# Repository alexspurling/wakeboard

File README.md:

# Wakeboard

A custom Kicad PCB based on the ESP32 and LIS3DH accelerometer. I built this to use as a low power device to detect when my washing machine starts and to send me a notification when it ends.

All files are open source under the Apache Licence 2.0

## Instructions for adding components

Since I wanted to order the PCB with JLCPCB, I wanted to ensure I picked parts that they have in stock. To do this, I used [easyeda2kicad](https://github.com/uPesy/easyeda2kicad.py) to pull the schematic, footprint and 3D model of a given LCSC part number. To run the script:

```
pip install easyeda2kicad
```

```
easyeda2kicad --full --lcsc_id=C2894897
```

This will copy files from EasyEDA (JLCPCB's own PCB creation tool) and save them into your `Documents/Kicad` directory.

From here, you can add this location as a library into KiCad to make all your downloaded components available:

* In KiCad, Go to Preferences > Configure Paths, and add the environment variables EASYEDA2KICAD :

    Windows : C:/Users/your_username/Documents/Kicad/easyeda2kicad/,
    Linux : /home/your_username/Documents/Kicad/easyeda2kicad/

* Go to Preferences > Manage Symbol Libraries, and Add the global library easyeda2kicad : ${EASYEDA2KICAD}/easyeda2kicad.kicad_sym
* Go to Preferences > Manage Footprint Libraries, and Add the global library easyeda2kicad : ${EASYEDA2KICAD}/easyeda2kicad.pretty

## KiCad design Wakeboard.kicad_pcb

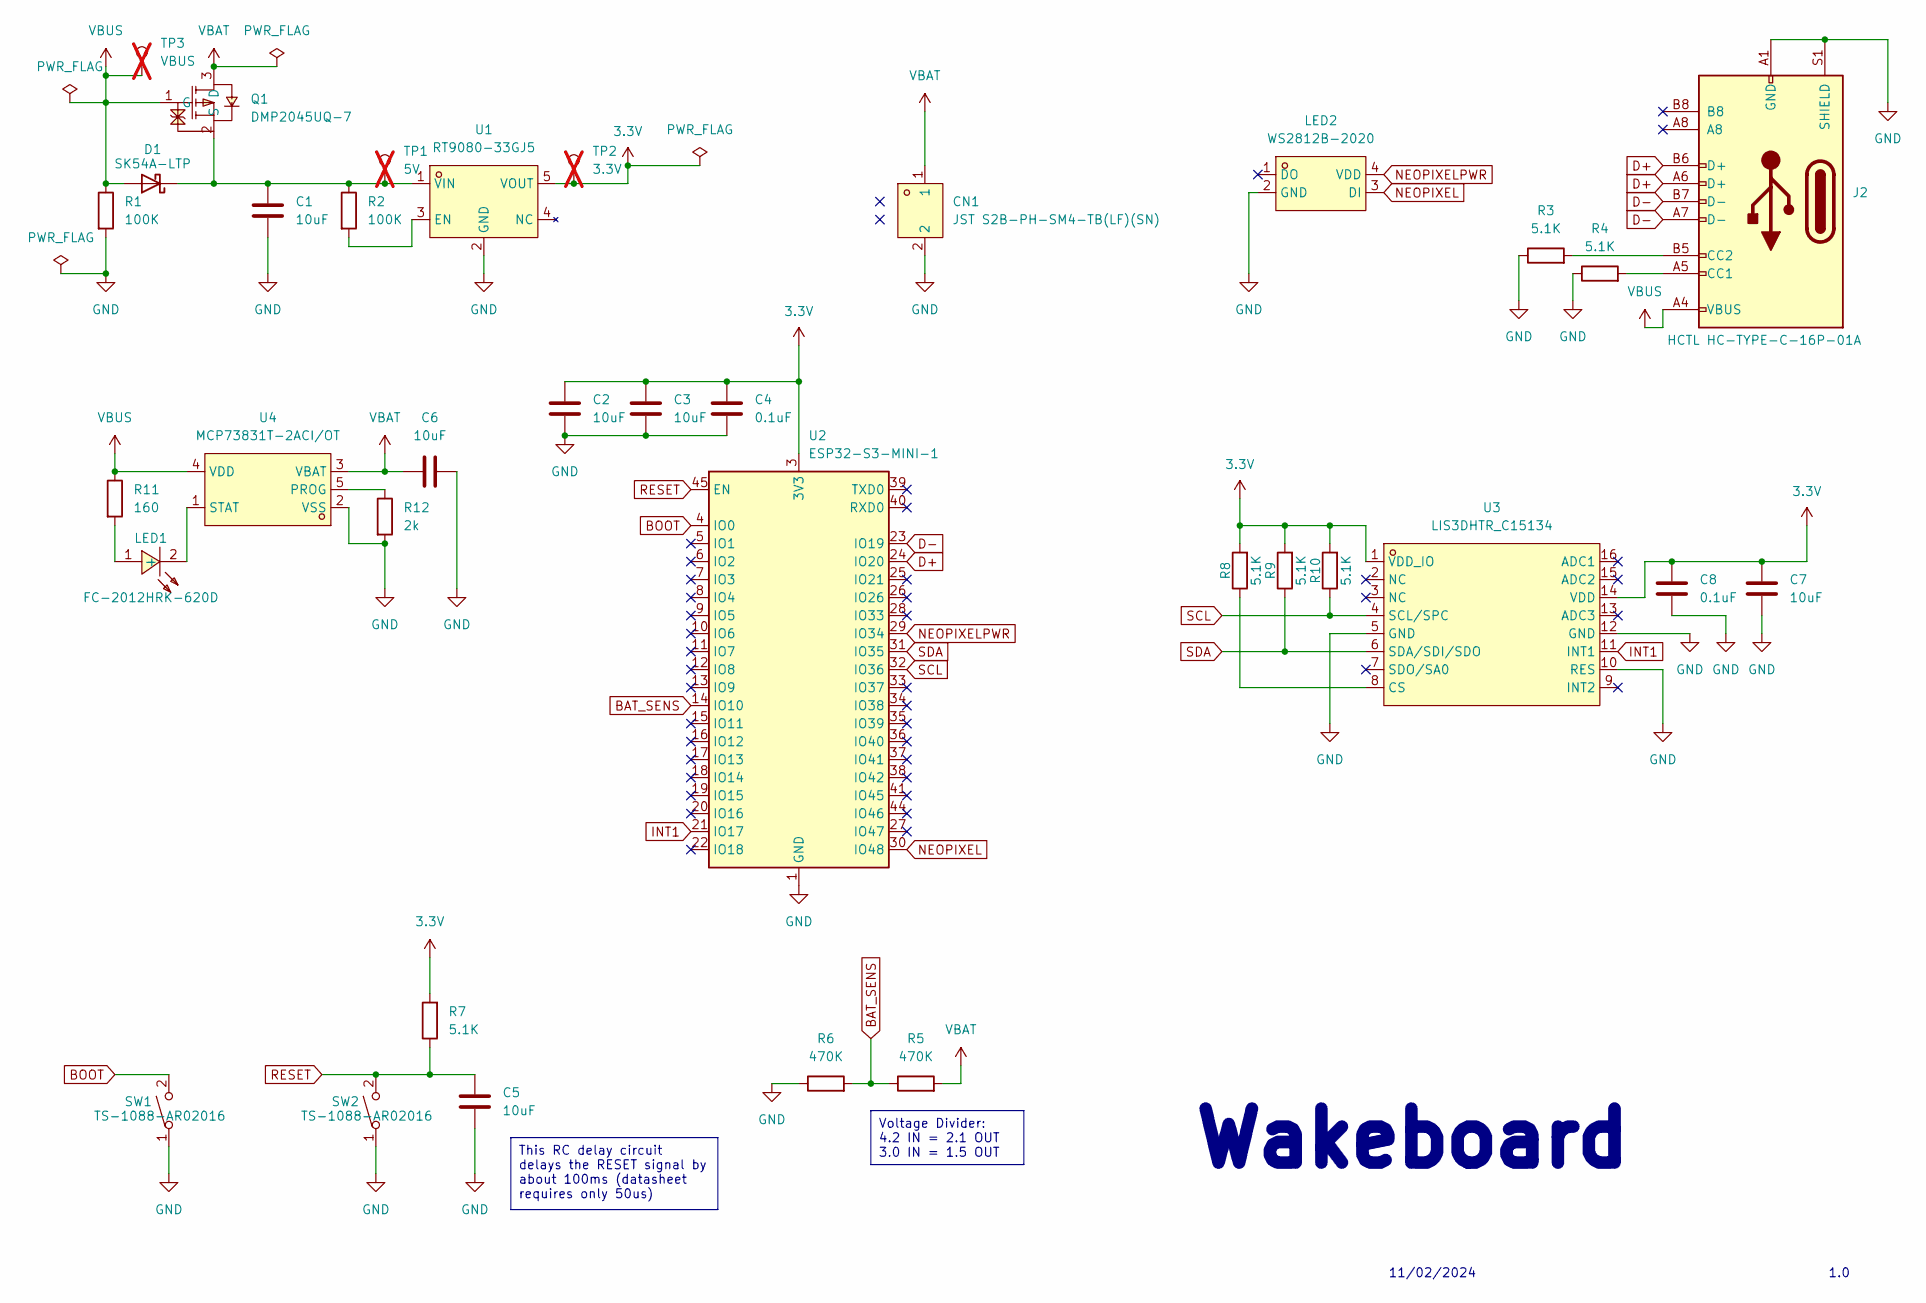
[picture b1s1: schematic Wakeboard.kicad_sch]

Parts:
C1, C2, C3, C5, C6, C7: 10uF; C_0805_2012Metric; LCSC Part C1713
C4, C8: 0.1uF; C_0805_2012Metric; LCSC Part C1711
CN1: JST S2B-PH-SM4-TB(LF)(SN); CONN-SMD_P2.00_S2B-PH-SM4-TB-LF-SN; LCSC Part C295747
D1: SK54A-LTP; D_SMA; LCSC Part C669017
J2: HCTL HC-TYPE-C-16P-01A; USB_C_Receptacle_HCTL_HC-TYPE-C-16P-01A; LCSC Part C2894897
LED1: FC-2012HRK-620D; LED0805-R-RD; LCSC Part C84256
LED2: WS2812B-2020; LED-SMD_4P-L2.0-W2.0-TL_WS2812B-2020; LCSC Part C965555
Q1: DMP2045UQ-7; SOT-23-3_L2.9-W1.3-P0.95-LS2.4-BR; LCSC Part C5157511
R1, R2: 100K; R_0805_2012Metric; LCSC Part C25611
R3, R4, R7, R8, R9, R10: 5.1K; R_0805_2012Metric; LCSC Part C26023
R5, R6: 470K; R_0805_2012Metric; LCSC Part C17709
R11: 160; R_0805_2012Metric; LCSC Part C25269
R12: 2k; R_0805_2012Metric; LCSC Part C17604
SW1, SW2: TS-1088-AR02016; SW-SMD_L3.9-W3.0-P4.45; LCSC Part C720477
TP1: 5V; TestPoint_Pad_D1.5mm; not fitted
TP2: 3.3V; TestPoint_Pad_D1.5mm; not fitted
TP3: VBUS; TestPoint_Pad_D1.5mm; not fitted
U1: RT9080-33GJ5; TSOT-23-5_L2.9-W1.6-P0.95-LS2.8-BL; LCSC Part C841192
U2: ESP32-S3-MINI-1; ESP32-S2-MINI-1; LCSC Part C2913206
U3: LIS3DHTR_C15134; LGA-16_L3.0-W3.0-P0.50-TL; LCSC Part C15134
U4: MCP73831T-2ACI/OT; SOT-23-5_L3.0-W1.7-P0.95-LS2.8-BL; LCSC Part C424093

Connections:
3.3V: C2.1, C3.1, C4.1, C7.1, C8.1, R7.2, R8.2, R9.2, R10.2, TP2.1, U1.5 (VOUT), U2.3 (3V3), U3.1 (VDD_IO), U3.14 (VDD)
BAT_SENS: R5.1, R6.2, U2.14 (IO10)
BOOT: SW1.2, U2.4 (IO0)
D+: J2.A6 (D+), J2.B6 (D+), U2.24 (IO20)
D-: J2.A7 (D-), J2.B7 (D-), U2.23 (IO19)
GND: C1.2, C2.2, C3.2, C4.2, C5.2, C6.2, C7.2, C8.2, CN1.2, J2.A1 (GND), J2.A12 (GND), J2.B1 (GND), J2.B12 (GND), J2.S1 (SHIELD), LED2.2 (GND), R1.2, R3.1, R4.1, R6.1, R12.2, SW1.1, SW2.1, U1.2 (GND), U2.1 (GND), U2.2 (GND), U2.42 (GND), U2.43 (GND), U2.46 (GND), U2.47 (GND), U2.48 (GND), U2.49 (GND), U2.50 (GND), U2.51 (GND), U2.52 (GND), U2.53 (GND), U2.54 (GND), U2.55 (GND), U2.56 (GND), U2.57 (GND), U2.58 (GND), U2.59 (GND), U2.60 (GND), U2.61 (GND), U2.62 (GND), U2.63 (GND), U2.64 (GND), U2.65 (GND), U3.5 (GND), U3.10 (RES), U3.12 (GND), U4.2 (VSS)
INT1: U2.21 (IO17), U3.11 (INT1)
NEOPIXEL: LED2.3 (DI), U2.30 (IO48)
NEOPIXELPWR: LED2.4 (VDD), U2.29 (IO34)
unnamed: C1.1, D1.1 (K), Q1.2 (S), R2.1, TP1.1, U1.1 (VIN)
unnamed: J2.A5 (CC1), R4.2
unnamed: J2.B5 (CC2), R3.2
unnamed: LED1.1 (+), R11.2
unnamed: LED1.2 (-), U4.1 (STAT)
unnamed: R2.2, U1.3 (EN)
unnamed: R8.1, U3.8 (CS)
unnamed: R12.1, U4.5 (PROG)
RESET: C5.1, R7.1, SW2.2, U2.45 (EN)
SCL: R10.1, U2.32 (IO36), U3.4 (SCL/SPC)
SDA: R9.1, U2.31 (IO35), U3.6 (SDA/SDI/SDO)
VBAT: C6.1, CN1.1, Q1.3 (D), R5.2, U4.3 (VBAT)
VBUS: D1.2 (A), J2.A4 (VBUS), J2.A9 (VBUS), J2.B4 (VBUS), J2.B9 (VBUS), Q1.1 (G), R1.1, R11.1, TP3.1, U4.4 (VDD)

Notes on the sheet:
This RC delay circuit delays the RESET signal by about 100ms (datasheet requires only 50us)
Voltage Divider: 4.2 IN = 2.1 OUT 3.0 IN = 1.5 OUT
1.0
11/02/2024
Wakeboard

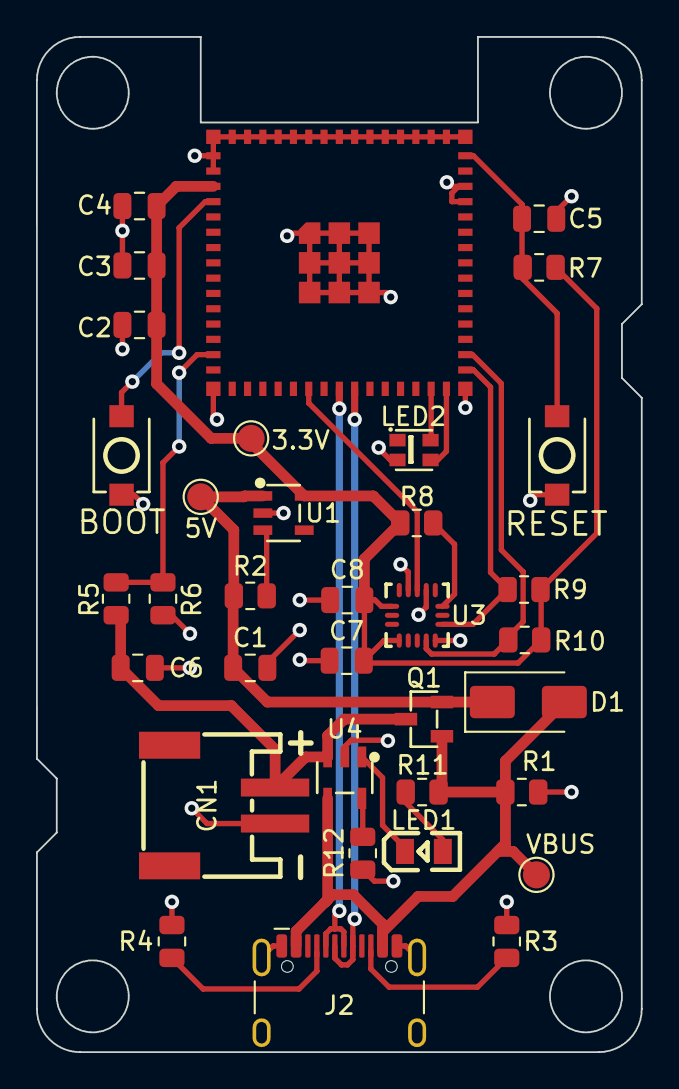
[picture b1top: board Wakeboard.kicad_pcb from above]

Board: 2 copper layers, 33.6 x 56.4 mm, 35 parts (0 on the bottom side), 22 nets.

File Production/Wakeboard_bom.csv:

"Reference","Value","Footprint","Qty","LCSC Part"
"C1,C2,C3,C5,C6,C7","10uF","Capacitor_SMD:C_0805_2012Metric","6","C1713"
"C4,C8","0.1uF","Capacitor_SMD:C_0805_2012Metric","2","C1711"
"CN1","JST S2B-PH-SM4-TB(LF)(SN)","easyeda2kicad:CONN-SMD_P2.00_S2B-PH-SM4-TB-LF-SN","1","C295747"
"D1","SK54A-LTP","Diode_SMD:D_SMA","1","C669017"
"J2","HCTL HC-TYPE-C-16P-01A","Connector_USB:USB_C_Receptacle_HCTL_HC-TYPE-C-16P-01A","1","C2894897"
"LED1","FC-2012HRK-620D","easyeda2kicad:LED0805-R-RD","1","C84256"
"LED2","WS2812B-2020","easyeda2kicad:LED-SMD_4P-L2.0-W2.0-TL_WS2812B-2020","1","C965555"
"Q1","DMP2045UQ-7","easyeda2kicad:SOT-23-3_L2.9-W1.3-P0.95-LS2.4-BR","1","C5157511"
"R1,R2","100K","Resistor_SMD:R_0805_2012Metric","2","C25611"
"R3,R4,R7,R8,R9,R10","5.1K","Resistor_SMD:R_0805_2012Metric","6","C26023"
"R5,R6","470K","Resistor_SMD:R_0805_2012Metric","2","C17709"
"R11","160","Resistor_SMD:R_0805_2012Metric","1","C25269"
"R12","2k","Resistor_SMD:R_0805_2012Metric","1","C17604"
"SW1,SW2","TS-1088-AR02016","easyeda2kicad:SW-SMD_L3.9-W3.0-P4.45","2","C720477"
"U1","RT9080-33GJ5","easyeda2kicad:TSOT-23-5_L2.9-W1.6-P0.95-LS2.8-BL","1","C841192"
"U2","ESP32-S3-MINI-1","RF_Module:ESP32-S2-MINI-1","1","C2913206"
"U3","LIS3DHTR_C15134","easyeda2kicad:LGA-16_L3.0-W3.0-P0.50-TL","1","C15134"
"U4","MCP73831T-2ACI/OT","easyeda2kicad:SOT-23-5_L3.0-W1.7-P0.95-LS2.8-BL","1","C424093"

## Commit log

2024-02-11 Washingboard
2024-02-12 PCB Layout
2024-02-14 PCB and Schematic v1.0
2024-02-14 Images
2024-02-14 Remove PCB below antenna. Swap SDA and SCL GPIO. Update interrupt to GPIO 21, battery level to GPIO 10.
2024-02-14 Add README and images
2024-02-14 Small update to PCB
2024-02-15 Add .gitignore
2024-02-15 Adding Gerber and BOM files
2024-02-15 Production files zip
2024-03-06 Shift battery socket
2024-03-07 Remove mounting holes. Fix minor things
2024-03-07 Enclosure OpenSCAD files
2024-03-07 Add USB hole
2024-03-07 Add supports. Set wall thickness to 2.6
2024-03-08 Add magnet holes. Add battery and PCB templates
2024-03-12 Enclosure with lid
2024-03-13 Snapfit lid
2024-03-13 Small recess on the base
2024-03-13 Export STL
2024-03-13 Split into base and lid
2024-03-14 Add cut outs to view LEDs
2024-03-15 Resize board
2024-03-15 Shift components after resize
2024-03-28 Production files for latest PCB
2024-03-31 Update 3D render
2024-03-31 Add photo
2024-04-01 Update PCB image
